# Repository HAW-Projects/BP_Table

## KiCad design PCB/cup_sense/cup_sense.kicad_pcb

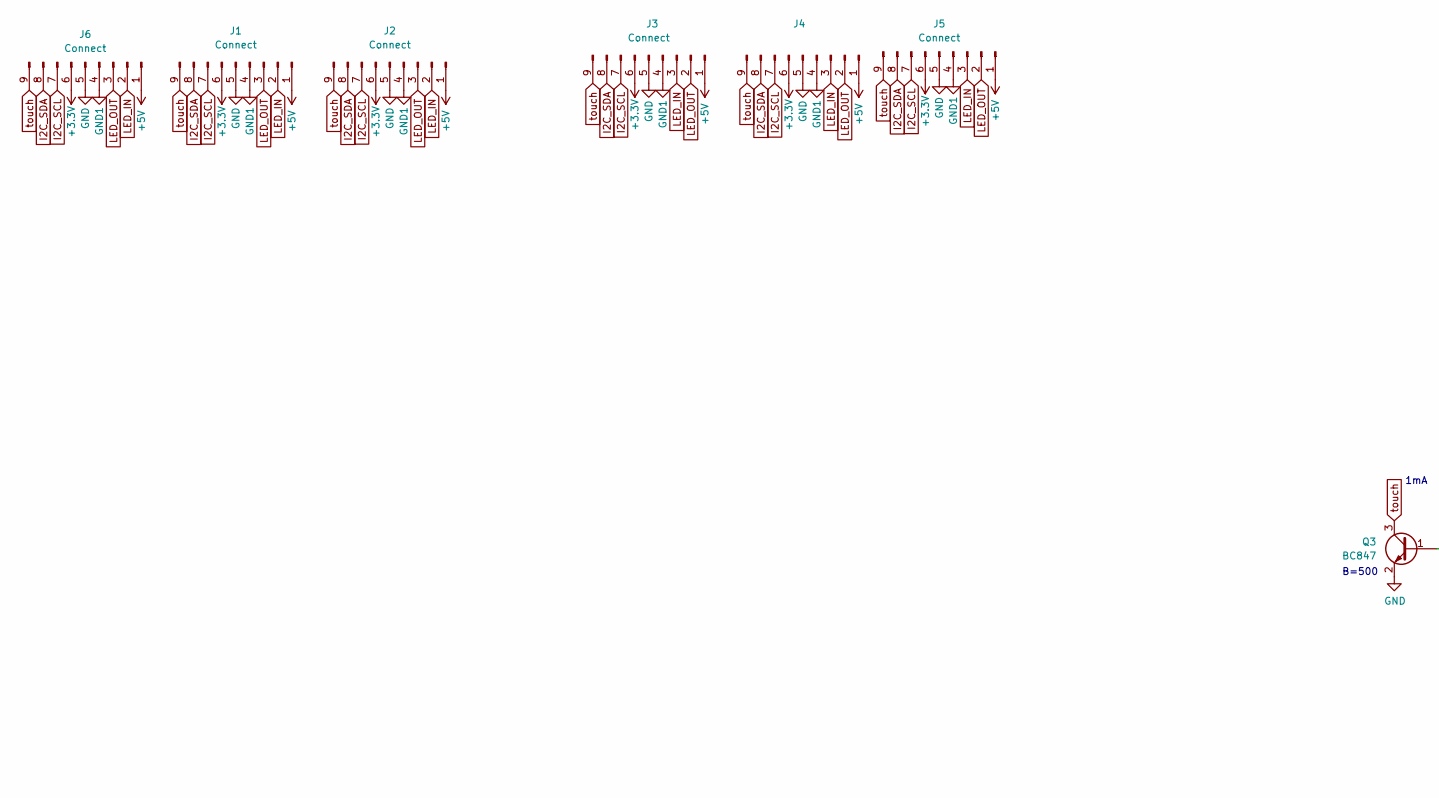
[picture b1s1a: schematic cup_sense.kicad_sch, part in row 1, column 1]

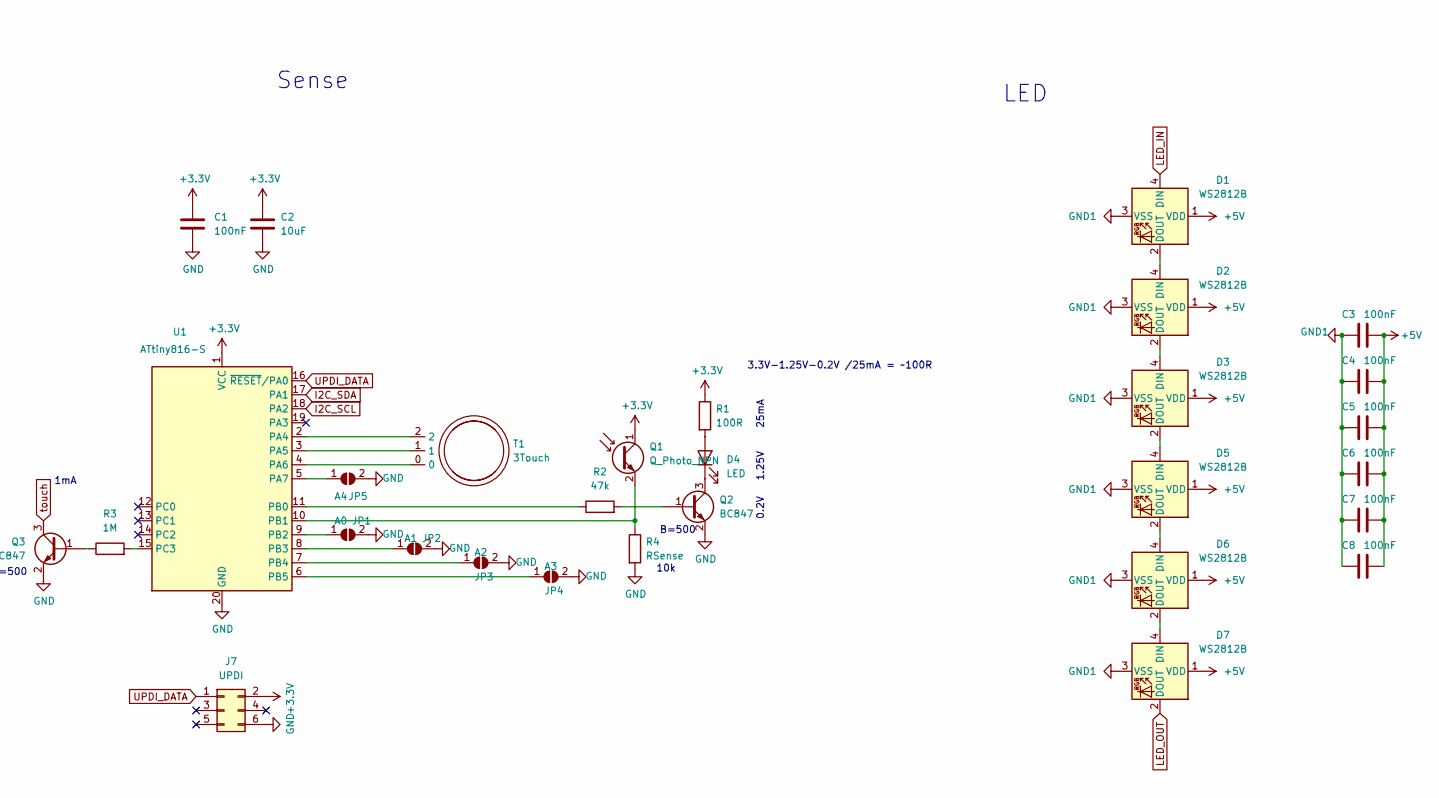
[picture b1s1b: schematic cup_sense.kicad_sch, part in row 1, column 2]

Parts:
C1, C3, C4, C5, C6, C7, C8: 100nF; C_0603_1608Metric
C2: 10uF; C_0805_2012Metric
D1, D2, D3, D5, D6, D7: WS2812B; LED_WS2812B_PLCC4_5.0x5.0mm_P3.2mm_handSolder
D4: LED; LED_RevMount_5mm
J1, J2, J6: Connect; 1x09_EdgeConnect_Flip
J3, J4, J5: Connect; 1x09_EdgeConnect
J7: UPDI; PinHeader_2x03_P2.54mm_Vertical
JP1: A0; SolderJumper-2_P1.3mm_Open_TrianglePad1.0x1.5mm
JP2: A1; SolderJumper-2_P1.3mm_Open_TrianglePad1.0x1.5mm
JP3: A2; SolderJumper-2_P1.3mm_Open_TrianglePad1.0x1.5mm
JP4: A3; SolderJumper-2_P1.3mm_Open_TrianglePad1.0x1.5mm
JP5: A4; SolderJumper-2_P1.3mm_Open_TrianglePad1.0x1.5mm
Q1: Q_Photo_NPN; LED_RevMount_5mm
Q2, Q3: BC847; SOT-323_SC-70
R1: 100R; R_0603_1608Metric
R2: 47k; R_0603_1608Metric
R3: 1M; R_0603_1608Metric
R4: RSense; R_0603_1608Metric
T1: 3Touch; 3Touch_80mm_back
U1: ATtiny816-S; SOIC-20W_7.5x12.8mm_P1.27mm

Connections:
+3V3: C1.1, C2.1, J1.6, J2.6, J3.6, J4.6, J5.6, J6.6, J7.2, Q1.1 (C), R1.1, U1.1 (VCC)
+5V: C3.2, C4.2, C5.2, C6.2, C7.2, C8.2, D1.1 (VDD), D2.1 (VDD), D3.1 (VDD), D5.1 (VDD), D6.1 (VDD), D7.1 (VDD), J1.1, J2.1, J3.1, J4.1, J5.1, J6.1
GND: C1.2, C2.2, J1.5, J2.5, J3.5, J4.5, J5.5, J6.5, J7.6, JP1.2 (B), JP2.2 (B), JP3.2 (B), JP4.2 (B), JP5.2 (B), Q2.2 (E), Q3.2 (E), R4.2, U1.20 (GND)
GND1: C3.1, C4.1, C5.1, C6.1, C7.1, C8.1, D1.3 (VSS), D2.3 (VSS), D3.3 (VSS), D5.3 (VSS), D6.3 (VSS), D7.3 (VSS), J1.4, J2.4, J3.4, J4.4, J5.4, J6.4
I2C_SCL: J1.7, J2.7, J3.7, J4.7, J5.7, J6.7, U1.18 (PA2)
I2C_SDA: J1.8, J2.8, J3.8, J4.8, J5.8, J6.8, U1.17 (PA1)
LED_IN: D1.4 (DIN), J1.2, J2.2, J3.3, J4.3, J5.3, J6.2
LED_OUT: D7.2 (DOUT), J1.3, J2.3, J3.2, J4.2, J5.2, J6.3
unnamed: D1.2 (DOUT), D2.4 (DIN)
unnamed: D2.2 (DOUT), D3.4 (DIN)
unnamed: D3.2 (DOUT), D5.4 (DIN)
unnamed: D4.1 (K), Q2.3 (C)
unnamed: D4.2 (A), R1.2
unnamed: D5.2 (DOUT), D6.4 (DIN)
unnamed: D6.2 (DOUT), D7.4 (DIN)
unnamed: JP1.1 (A), U1.9 (PB2)
unnamed: JP2.1 (A), U1.8 (PB3)
unnamed: JP3.1 (A), U1.7 (PB4)
unnamed: JP4.1 (A), U1.6 (PB5)
unnamed: JP5.1 (A), U1.5 (PA7)
unnamed: Q1.2 (E), R4.1, U1.10 (PB1)
unnamed: Q2.1 (B), R2.2
unnamed: Q3.1 (B), R3.1
unnamed: R2.1, U1.11 (PB0)
unnamed: R3.2, U1.15 (PC3)
unnamed: T1.0, U1.4 (PA6)
unnamed: T1.1, U1.3 (PA5)
unnamed: T1.2, U1.2 (PA4)
UPDI_DATA: J7.1, U1.16 (~RESET/PA0)
touch: J1.9, J2.9, J3.9, J4.9, J5.9, J6.9, Q3.3 (C)

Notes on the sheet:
B=500
1mA
0.2V
Sense
3.3V-1.25V-0.2V /25mA = ~100R
10k
1.25V
LED
25mA

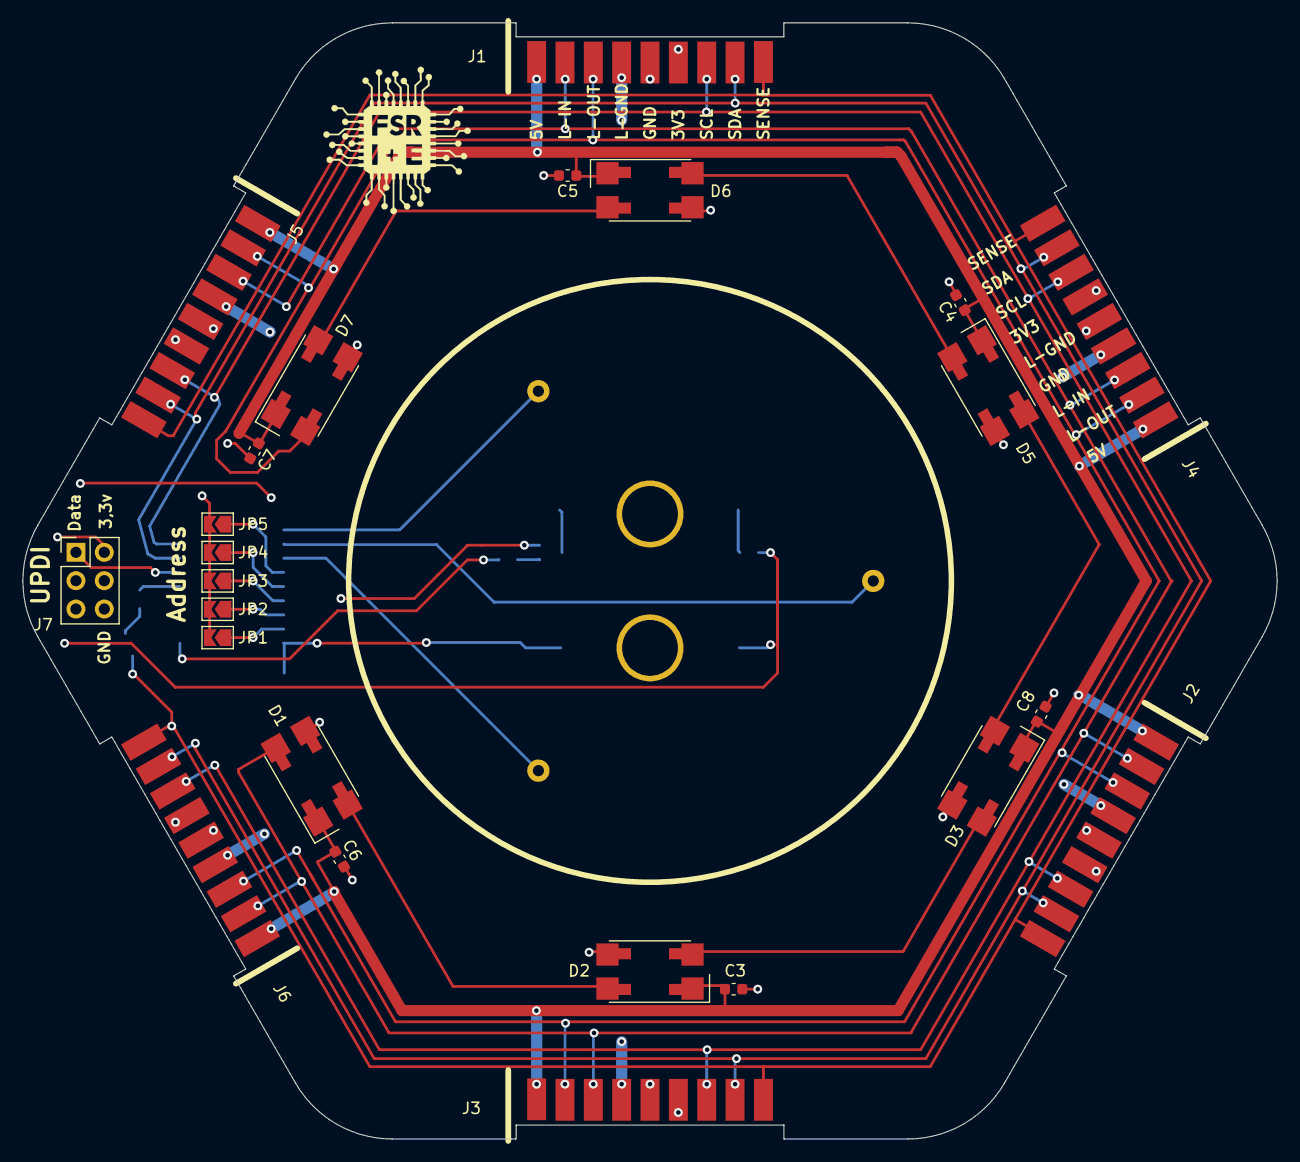
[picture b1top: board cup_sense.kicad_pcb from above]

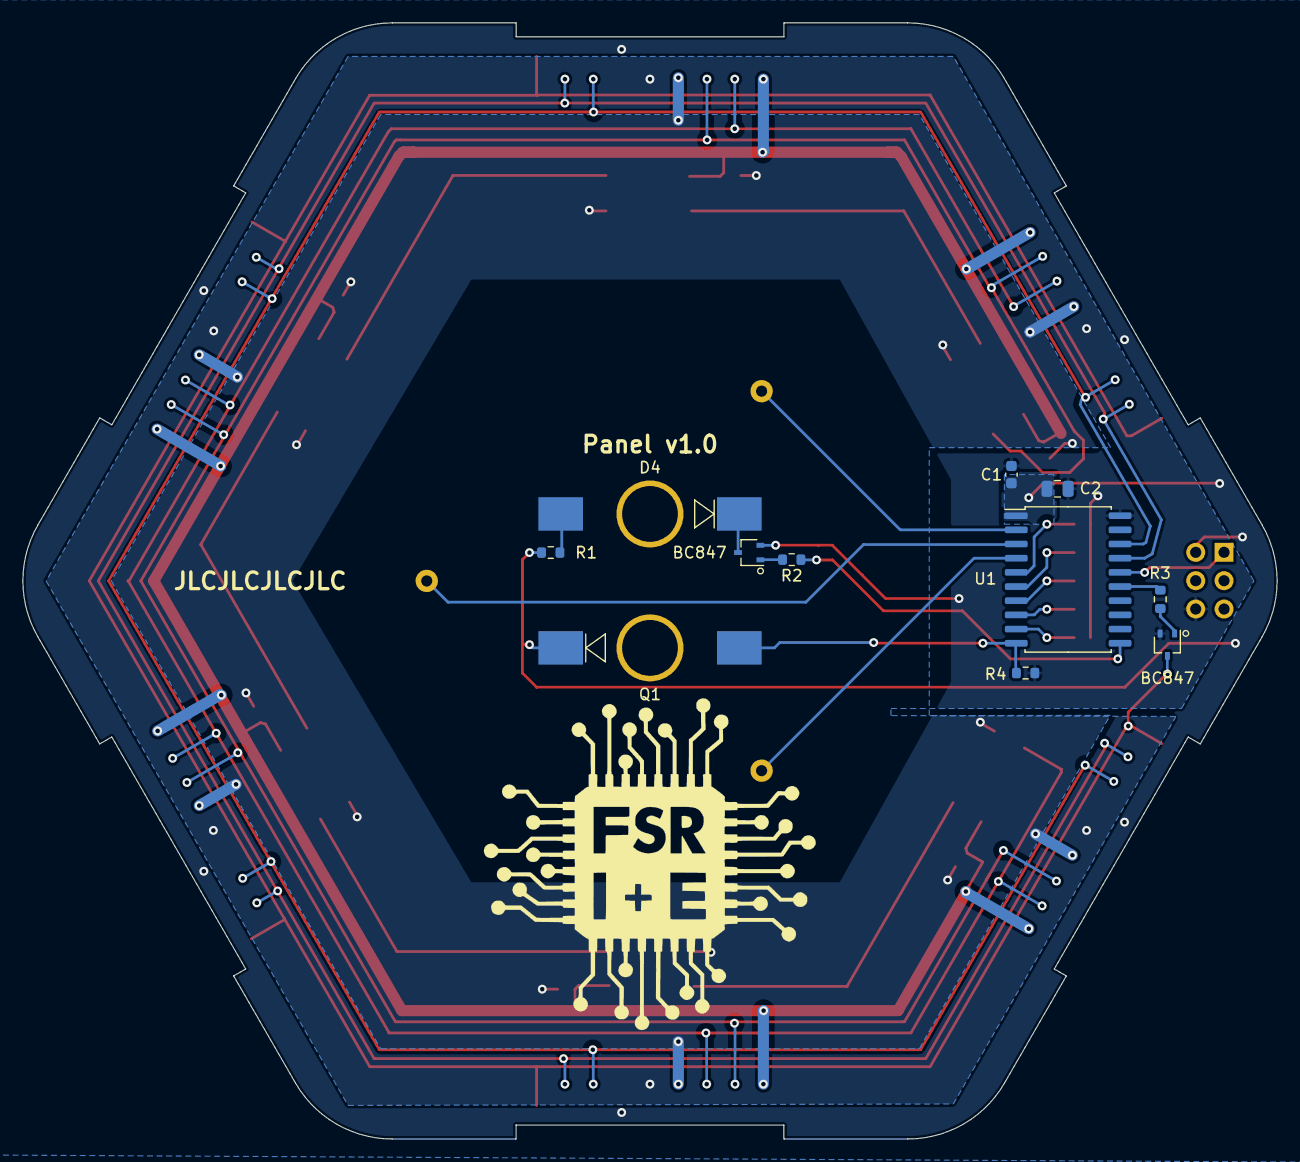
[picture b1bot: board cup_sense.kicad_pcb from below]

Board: 2 copper layers, 112.4 x 100.0 mm, 36 parts (9 on the bottom side), 30 nets.

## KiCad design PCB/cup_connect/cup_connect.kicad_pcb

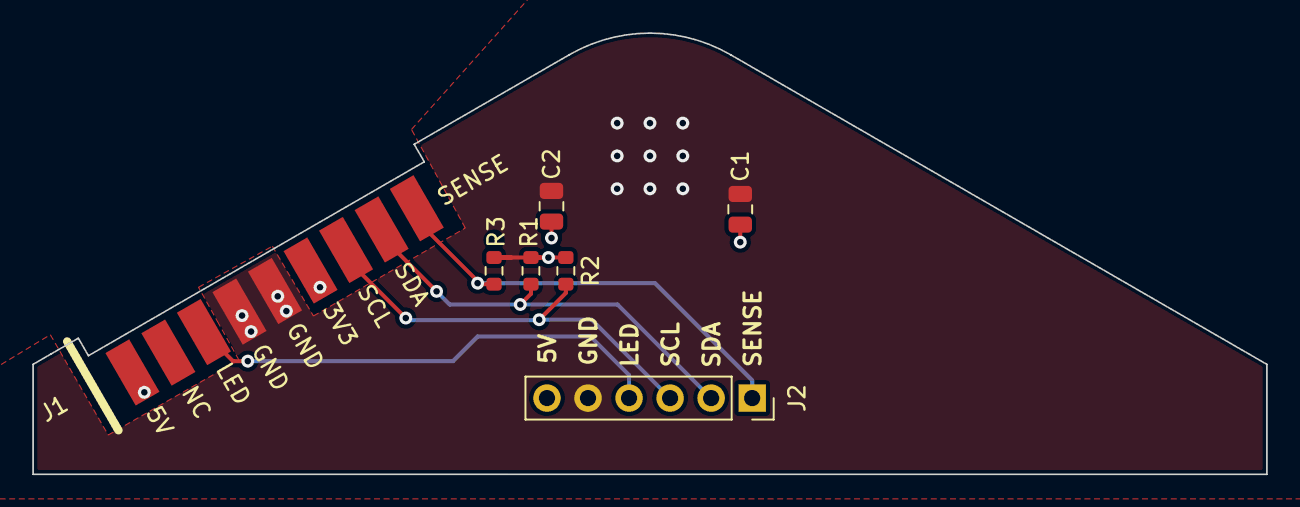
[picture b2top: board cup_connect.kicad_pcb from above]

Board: 2 copper layers, 76.4 x 27.3 mm, 8 parts (1 on the bottom side), 7 nets.

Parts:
C1, C2: 10uF; C_0805_2012Metric
J1: Connect; 1x09_EdgeConnect_Flip
J2: Conn_01x06_Female; PinSocket_1x06_P2.54mm_Vertical
R1, R2: 2k2; R_0603_1608Metric
R3: 1k; R_0603_1608Metric
U1: LF30; TO-252-2

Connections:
+3V3: C2.1, J1.6, R1.2, R2.2, R3.2, U1.3 (VO)
+5V: C1.1, J1.1, J2.6, U1.1 (VI)
GND: C1.2, C2.2, J1.4, J1.5, J2.5, U1.2 (GND)
I2C_SCL: J1.7, J2.3, R2.1
I2C_SDA: J1.8, J2.2, R1.1
LED_IN: J1.3, J2.4
touch: J1.9, J2.1, R3.1

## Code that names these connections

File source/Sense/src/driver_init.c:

/**
 * \file
 *
 * \brief Driver initialization.
 *
 (c) 2020 Microchip Technology Inc. and its subsidiaries.

    Subject to your compliance with these terms,you may use this software and
    any derivatives exclusively with Microchip products.It is your responsibility
    to comply with third party license terms applicable to your use of third party
    software (including open source software) that may accompany Microchip software.

    THIS SOFTWARE IS SUPPLIED BY MICROCHIP "AS IS". NO WARRANTIES, WHETHER
    EXPRESS, IMPLIED OR STATUTORY, APPLY TO THIS SOFTWARE, INCLUDING ANY IMPLIED
    WARRANTIES OF NON-INFRINGEMENT, MERCHANTABILITY, AND FITNESS FOR A
    PARTICULAR PURPOSE.

    IN NO EVENT WILL MICROCHIP BE LIABLE FOR ANY INDIRECT, SPECIAL, PUNITIVE,
    INCIDENTAL OR CONSEQUENTIAL LOSS, DAMAGE, COST OR EXPENSE OF ANY KIND
    WHATSOEVER RELATED TO THE SOFTWARE, HOWEVER CAUSED, EVEN IF MICROCHIP HAS
    BEEN ADVISED OF THE POSSIBILITY OR THE DAMAGES ARE FORESEEABLE. TO THE
    FULLEST EXTENT ALLOWED BY LAW, MICROCHIP'S TOTAL LIABILITY ON ALL CLAIMS IN
    ANY WAY RELATED TO THIS SOFTWARE WILL NOT EXCEED THE AMOUNT OF FEES, IF ANY,
    THAT YOU HAVE PAID DIRECTLY TO MICROCHIP FOR THIS SOFTWARE.
 *
 */

/*
 * Code generated by START.
 *
 * This file will be overwritten when reconfiguring your START project.
 * Please copy examples or other code you want to keep to a separate file
 * to avoid losing it when reconfiguring.
 */

#include "driver_init.h"
#include <system.h>

/* Configure pins and initialize registers */
void ADC_0_initialization(void) {

    // Disable digital input buffer
    IR_SENSE_set_isc(PORT_ISC_INPUT_DISABLE_gc);
    // Disable pull-up resistor
    IR_SENSE_set_pull_mode(PORT_PULL_OFF);

    ADC_0_init();
}

/* configure pins and initialize registers */
void I2C_0_initialization(void) {

    PA2_set_level(
        // <y> Initial level
        // <id> pad_initial_level
        // <false"> Low
        // <true"> High
        false);

    PA2_set_dir(
        // <y> Pin direction
        // <id> pad_dir
        // <PORT_DIR_OFF"> Off
        // <PORT_DIR_IN"> In
        // <PORT_DIR_OUT"> Out
        PORT_DIR_OUT);

    PA2_set_pull_mode(
        // <y> Pull configuration
        // <id> pad_pull_config
        // <PORT_PULL_OFF"> Off
        // <PORT_PULL_UP"> Pull-up
        PORT_PULL_OFF);

    PA2_set_inverted(
        // <y> Invert I/O on pin
        // <id> pad_invert
        // <false"> Not inverted
        // <true"> Inverted
        false);

    PA2_set_isc(
        // <y> Pin Input/Sense Configuration
        // <id> pad_isc
        // <PORT_ISC_INTDISABLE_gc"> Interrupt disabled but input buffer enabled
        // <PORT_ISC_BOTHEDGES_gc"> Sense Both Edges
        // <PORT_ISC_RISING_gc"> Sense Rising Edge
        // <PORT_ISC_FALLING_gc"> Sense Falling Edge
        // <PORT_ISC_INPUT_DISABLE_gc"> Digital Input Buffer disabled
        // <PORT_ISC_LEVEL_gc"> Sense low Level
        PORT_ISC_INTDISABLE_gc);

    /* set the alternate pin mux */
    PORTMUX.CTRLB |= PORTMUX_TWI0_bm;

    PA1_set_level(
        // <y> Initial level
        // <id> pad_initial_level
        // <false"> Low
        // <true"> High
        false);

    PA1_set_dir(
        // <y> Pin direction
        // <id> pad_dir
        // <PORT_DIR_OFF"> Off
        // <PORT_DIR_IN"> In
        // <PORT_DIR_OUT"> Out
        PORT_DIR_OUT);

    PA1_set_pull_mode(
        // <y> Pull configuration
        // <id> pad_pull_config
        // <PORT_PULL_OFF"> Off
        // <PORT_PULL_UP"> Pull-up
        PORT_PULL_OFF);

    PA1_set_inverted(
        // <y> Invert I/O on pin
        // <id> pad_invert
        // <false"> Not inverted
        // <true"> Inverted
        false);

    PA1_set_isc(
        // <y> Pin Input/Sense Configuration
        // <id> pad_isc
        // <PORT_ISC_INTDISABLE_gc"> Interrupt disabled but input buffer enabled
        // <PORT_ISC_BOTHEDGES_gc"> Sense Both Edges
        // <PORT_ISC_RISING_gc"> Sense Rising Edge
        // <PORT_ISC_FALLING_gc"> Sense Falling Edge
        // <PORT_ISC_INPUT_DISABLE_gc"> Digital Input Buffer disabled
        // <PORT_ISC_LEVEL_gc"> Sense low Level
        PORT_ISC_INTDISABLE_gc);

    /* set the alternate pin mux */
    PORTMUX.CTRLB |= PORTMUX_TWI0_bm;

    I2C_0_init();
}

/**
 * \brief System initialization
 */
void system_init() {
    mcu_init();

    /* PORT setting on PA7 */

    // Set pin direction to input
    A4_set_dir(PORT_DIR_IN);

    A4_set_pull_mode(
        // <y> Pull configuration
        // <id> pad_pull_config
        // <PORT_PULL_OFF"> Off
        // <PORT_PULL_UP"> Pull-up
        PORT_PULL_UP);

    /* PORT setting on PB0 */

    // Set pin direction to output

    IR_LED_set_level(
        // <y> Initial level
        // <id> pad_initial_level
        // <false"> Low
        // <true"> High
        false);

    IR_LED_set_dir(PORT_DIR_OUT);

    /* PORT setting on PB2 */

    // Set pin direction to input
    A0_set_dir(PORT_DIR_IN);

    A0_set_pull_mode(
        // <y> Pull configuration
        // <id> pad_pull_config
        // <PORT_PULL_OFF"> Off
        // <PORT_PULL_UP"> Pull-up
        PORT_PULL_UP);

    /* PORT setting on PB3 */

    // Set pin direction to input
    A1_set_dir(PORT_DIR_IN);

    A1_set_pull_mode(
        // <y> Pull configuration
        // <id> pad_pull_config
        // <PORT_PULL_OFF"> Off
        // <PORT_PULL_UP"> Pull-up
        PORT_PULL_UP);

    /* PORT setting on PB4 */

    // Set pin direction to input
    A2_set_dir(PORT_DIR_IN);

    A2_set_pull_mode(
        // <y> Pull configuration
        // <id> pad_pull_config
        // <PORT_PULL_OFF"> Off
        // <PORT_PULL_UP"> Pull-up
        PORT_PULL_UP);

    /* PORT setting on PB5 */

    // Set pin direction to input
    A3_set_dir(PORT_DIR_IN);

    A3_set_pull_mode(
        // <y> Pull configuration
        // <id> pad_pull_config
        // <PORT_PULL_OFF"> Off
        // <PORT_PULL_UP"> Pull-up
        PORT_PULL_UP);

    /* PORT setting on PC3 */

    // Set pin direction to output

    sense_trig_set_level(
        // <y> Initial level
        // <id> pad_initial_level
        // <false"> Low
        // <true"> High
        false);

    sense_trig_set_dir(PORT_DIR_OUT);

    CLKCTRL_init();

    Timer_init();

    ADC_0_initialization();

    CPUINT_init();

    SLPCTRL_init();

    I2C_0_initialization();

    BOD_init();
}

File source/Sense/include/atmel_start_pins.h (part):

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#include <port.h>

/**
 * \brief Set PA1 pull mode
 *
 * Configure pin to pull up, down or disable pull mode, supported pull
 * modes are defined by device used
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}

/**
 * \brief Set PA1 data direction
 *
 * Select if the pin data direction is input, output or disabled.
 * If disabled state is not possible, this function throws an assert.
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}

/**
 * \brief Set PA1 input/sense configuration
 *
 * Enable/disable PA1 digital input buffer and pin change interrupt,
 * select pin interrupt edge/level sensing mode
 *
 * \param[in] isc PORT_ISC_INTDISABLE_gc    = Iterrupt disabled but input buffer enabled
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}

/**
 * \brief Set PA1 inverted mode
 *
 * Enable or disable inverted I/O on a pin
 *
 * \param[in] inverted true  = I/O on PA1 is inverted
 *                     false = I/O on PA1 is not inverted
 */
static inline void PA1_set_inverted(const bool inverted) {
    PORTA_pin_set_inverted(1, inverted);
}

/**
 * \brief Set PA1 level
 *
 * Sets output level on a pin
 *
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}

/**
 * \brief Toggle output level on PA1
 *
 * Toggle the pin level
 */
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}

/**
 * \brief Get level on PA1
 *
 * Reads the level on a pin
 */
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}

/**
 * \brief Set PA2 pull mode
 *
 * Configure pin to pull up, down or disable pull mode, supported pull
 * modes are defined by device used
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}

/**
 * \brief Set PA2 data direction
 *
 * Select if the pin data direction is input, output or disabled.
 * If disabled state is not possible, this function throws an assert.
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}

/**
 * \brief Set PA2 input/sense configuration
 *
 * Enable/disable PA2 digital input buffer and pin change interrupt,
 * select pin interrupt edge/level sensing mode
 *
 * \param[in] isc PORT_ISC_INTDISABLE_gc    = Iterrupt disabled but input buffer enabled
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}

/**
 * \brief Set PA2 inverted mode
 *
 * Enable or disable inverted I/O on a pin
 *
 * \param[in] inverted true  = I/O on PA2 is inverted
 *                     false = I/O on PA2 is not inverted
 */
static inline void PA2_set_inverted(const bool inverted) {
    PORTA_pin_set_inverted(2, inverted);
}

/**
 * \brief Set PA2 level
 *
 * Sets output level on a pin
 *
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}

/**
 * \brief Toggle output level on PA2
 *
 * Toggle the pin level
 */
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}

/**
 * \brief Get level on PA2
 *
 * Reads the level on a pin
 */
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}

/**
 * \brief Set PA4 pull mode
 *
 * Configure pin to pull up, down or disable pull mode, supported pull
 * modes are defined by device used
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}

/**
 * \brief Set PA4 data direction
 *
 * Select if the pin data direction is input, output or disabled.
 * If disabled state is not possible, this function throws an assert.
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}

/**
 * \brief Set PA4 input/sense configuration
 *
 * Enable/disable PA4 digital input buffer and pin change interrupt,
 * select pin interrupt edge/level sensing mode
 *
 * \param[in] isc PORT_ISC_INTDISABLE_gc    = Iterrupt disabled but input buffer enabled
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}

/**
 * \brief Set PA4 inverted mode
 *
 * Enable or disable inverted I/O on a pin
 *
 * \param[in] inverted true  = I/O on PA4 is inverted
 *                     false = I/O on PA4 is not inverted
 */
static inline void PA4_set_inverted(const bool inverted) {
    PORTA_pin_set_inverted(4, inverted);
}

/**
 * \brief Set PA4 level
 *
 * Sets output level on a pin
 *
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}

/**
 * \brief Toggle output level on PA4
 *
 * Toggle the pin level
 */
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}

/**
 * \brief Get level on PA4
 *
 * Reads the level on a pin
 */
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}

/**
 * \brief Set PA5 pull mode
 *
 * Configure pin to pull up, down or disable pull mode, supported pull
 * modes are defined by device used
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}

/**
 * \brief Set PA5 data direction
 *
 * Select if the pin data direction is input, output or disabled.
 * If disabled state is not possible, this function throws an assert.
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}

/**
 * \brief Set PA5 input/sense configuration
 *
 * Enable/disable PA5 digital input buffer and pin change interrupt,
 * select pin interrupt edge/level sensing mode
 *
 * \param[in] isc PORT_ISC_INTDISABLE_gc    = Iterrupt disabled but input buffer enabled
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}

/**
 * \brief Set PA5 inverted mode
 *
 * Enable or disable inverted I/O on a pin
 *
 * \param[in] inverted true  = I/O on PA5 is inverted
 *                     false = I/O on PA5 is not inverted
 */
static inline void PA5_set_inverted(const bool inverted) {
    PORTA_pin_set_inverted(5, inverted);
}

/**
 * \brief Set PA5 level
 *
 * Sets output level on a pin
 *
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}

/**
 * \brief Toggle output level on PA5
 *
 * Toggle the pin level
 */
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}

/**
 * \brief Get level on PA5
 *
 * Reads the level on a pin
 */
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}

/**
 * \brief Set PA6 pull mode
 *
 * Configure pin to pull up, down or disable pull mode, supported pull
 * modes are defined by device used
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}

/**
 * \brief Set PA6 data direction
 *
 * Select if the pin data direction is input, output or disabled.
 * If disabled state is not possible, this function throws an assert.
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}

/**
 * \brief Set PA6 input/sense configuration
 *
 * Enable/disable PA6 digital input buffer and pin change interrupt,
 * select pin interrupt edge/level sensing mode
 *
 * \param[in] isc PORT_ISC_INTDISABLE_gc    = Iterrupt disabled but input buffer enabled
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}

/**
 * \brief Set PA6 inverted mode
 *
 * Enable or disable inverted I/O on a pin
 *
 * \param[in] inverted true  = I/O on PA6 is inverted
 *                     false = I/O on PA6 is not inverted
 */
static inline void PA6_set_inverted(const bool inverted) {
    PORTA_pin_set_inverted(6, inverted);
}

/**
 * \brief Set PA6 level
 *
 * Sets output level on a pin
 *
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}

/**
 * \brief Toggle output level on PA6
 *
 * Toggle the pin level
 */
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}

/**
 * \brief Get level on PA6
 *
 * Reads the level on a pin
 */
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
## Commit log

2022-06-08 v1.0
2023-01-07 fix schematic values
